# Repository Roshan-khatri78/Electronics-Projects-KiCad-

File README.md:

# ⚡ KiCad Projects Portfolio

A growing collection of electronics projects designed in **KiCad** — schematics, PCB layouts, and Gerber files. Built as part of my hands-on learning journey in electronics engineering and PCB design.

---

## 📖 About

These projects range from beginner circuits to progressively complex PCB designs. Each one reflects real learning — including mistakes, revisions, and improvements over time. I add new projects regularly as I continue to grow.

**Skills practiced:**
- Schematic capture & symbol assignment
- PCB layout & trace routing
- Footprint selection & custom footprint creation
- Copper pours, DRC, and design rules
- Gerber file export for fabrication
- 3D model linking & visualization
- Hierarchical schematics & multi-sheet designs
- Custom symbol and footprint library creation

---

## 🗂️ Projects

### 1. [1-Channel Relay Driver](./1channelrelay/)
A single-channel relay driver PCB using an NPN transistor (MMBT2222A) to switch a Fujitsu FTR-LYCA005x relay from a microcontroller signal. Includes a flyback diode for back-EMF protection and a decoupling capacitor. All SMD components with a GND copper pour.
- **Key components:** MMBT2222A, FTR-LYCA005x relay, 1N4148 flyback diode
- **Concepts:** NPN switching, flyback protection, SMD layout, copper pour

### 2. [3-Phase BLDC Motor Controller](./3-Phase%20BLDC%20(Brushless%20DC)%20Motor%20Controller/)
A hierarchical, multi-sheet PCB design for driving a 3-phase brushless DC motor, using IR2104 half-bridge gate drivers to switch a 3-phase MOSFET bridge.
- **Key components:** IR2104 gate driver ICs, 3-phase MOSFET bridge
- **Concepts:** Hierarchical schematic design, gate driver circuits, 3-phase commutation, ERC debugging across multiple sheets

### 3. [Battery Desulfator Circuit](./Battery%20Desulfator%20circuit/)
An NE555-based pulse generator circuit designed to desulfate lead-acid batteries by sending high-frequency pulses to break down lead sulfate crystals on battery plates. Uses the DISCH pin (pin 7) to drive an IRF244V MOSFET and a flyback inductor (L1).
- **Key components:** NE555 timer IC, IRF244V MOSFET
- **Concepts:** 555 astable mode, pulse generation, MOSFET gate drive, battery maintenance circuits

### 4. [3V to 40V DC Booster](./3v%20to%2040v%20DC%20booster/)
A DC-DC boost converter PCB that steps up voltage from 3V to up to 40V. Designed for applications requiring higher voltages from low-voltage power supplies.
- **Concepts:** Boost converter topology, inductor selection, PCB layout for power electronics

### 5. [60W SMPS](./60w%20smps/)
A 60-watt Switch-Mode Power Supply (SMPS) PCB design. SMPS circuits offer high efficiency compared to linear regulators by using high-frequency switching to regulate output voltage.
- **Concepts:** Switching power supply topology, high-frequency PCB layout, power conversion, isolation

### 6. [Air Quality Sensor Board](./Air%20Quality%20Sensor%20Board/)
A sensor board PCB for monitoring air quality, pairing an air quality sensor with a microcontroller interface and a Tag-Connect SWD programming footprint for debugging.
- **Key components:** Air quality sensor IC, MCU, Tag-Connect SWD header
- **Concepts:** Analog sensor interfacing, board outline (Edge.Cuts) definition, DRC-clean layout, SWD footprint sourcing

### 7. [Arduino Uno R3 Clone](./Arduino%20R3/)
A faithful clone of the classic Arduino Uno R3, built around the ATmega328P microcontroller, replicating the original reference design.
- **Key components:** ATmega328P (DIP-28), 16MHz crystal, USB-to-serial interface
- **Concepts:** Reference design replication, footprint/symbol matching, copper pour strategy, through-hole MCU layout

### 8. [DC-DC Buck Converter (XL4015 CC/CV)](./DC-DC%20Buck%20converter/)
A step-down converter PCB based on the XL4015 IC, providing constant-current/constant-voltage (CC/CV) regulated output for charging and general power applications.
- **Key components:** XL4015 buck converter IC
- **Concepts:** CC/CV regulation, power inductor selection, feedback loop layout, thermal considerations

### 9. [DS3231 RTC Module](./DS3231%20RTC%20Module/)
A real-time clock breakout board built around the DS3231 high-precision RTC IC with battery backup, for timekeeping in embedded systems.
- **Key components:** DS3231 RTC IC, coin cell battery backup
- **Concepts:** RTC interfacing over I2C, battery backup circuit design, breakout board layout

### 10. [HC-06 Bluetooth Module](./HC-06%20BLUETOOTH%C2%AE%20Module/)
A breakout/reference design board for the HC-06 Bluetooth serial module, enabling wireless UART communication for microcontroller projects.
- **Key components:** HC-06 Bluetooth serial module
- **Concepts:** Module-level symbol/footprint sourcing, wireless UART bridging, breakout board design

### 11. [Induction Heater](./inductionheater/)
An induction heater circuit PCB. Uses high-frequency switching to generate an alternating magnetic field in a work coil, inducing eddy currents in conductive materials to produce heat.
- **Concepts:** High-frequency switching, resonant circuits, power PCB layout

### 12. [Mini Inverter](./mini%20inverter/)
A mini inverter circuit using IR2153 gate drive circuitry to convert DC to AC. The IR2153 provides high-side and low-side gate drive signals for a half-bridge MOSFET configuration.
- **Key components:** IR2153 gate driver
- **Concepts:** DC-AC inversion, gate drive circuits, half-bridge topology, IR2153 oscillator

### 13. [L298 Motor Driver](./L298%20motor%20driver/)
A motor driver PCB based on the L298N dual H-bridge IC, capable of driving two DC motors or one stepper motor with direction and speed control. Designed with onboard power regulation and protection diodes.
- **Key components:** L298N dual H-bridge IC
- **Concepts:** H-bridge motor control, dual DC/stepper motor drive, flyback diode protection, PCB layout for moderate current loads

### 14. [LED Flasher](./LED%20flasher/)
A simple astable multivibrator LED flasher circuit. A foundational circuit demonstrating oscillator design and timing with discrete components or a 555 timer.
- **Concepts:** Astable oscillator, RC timing, LED drive, beginner PCB layout

### 15. [SPO2 (Pulse Oximeter)](./SPO2/)
A pulse oximeter circuit PCB for measuring blood oxygen saturation (SpO2) and heart rate. Uses IR and red LEDs with a photodetector to sense light absorption differences in oxygenated vs. deoxygenated blood.
- **Concepts:** Optical sensing, analog signal conditioning, biopotential measurement, photodetector interfacing

### 16. [STM32 DEV Board](./STM32%20DEV%20board/)
A custom development board PCB for the STM32 microcontroller family. Includes necessary support circuitry such as decoupling capacitors, reset circuitry, boot mode selection, and programming headers.
- **Key components:** STM32 microcontroller
- **Concepts:** Microcontroller PCB design, power decoupling, SWD/JTAG programming interface, crystal oscillator layout

### 17. [USB to UART Converter](./USB2UART/)
A USB-to-UART bridge PCB for serial communication between a PC and embedded systems. Used for programming and debugging microcontrollers that lack native USB support.
- **Key components:** USB-UART bridge IC (e.g. CH340/CP2102)
- **Concepts:** USB full-speed interface, UART protocol, level shifting, USB connector footprint, ESD protection

### 18. [ESP32 Demo Project](./esp32%20demo%20project/)
A demonstration PCB built around the ESP32 module, exploring its GPIO, power, and communication capabilities. Serves as a base reference design for ESP32-based projects.
- **Key components:** ESP32 module
- **Concepts:** ESP32 power requirements, decoupling, RF layout considerations, boot mode strapping pins

### 19. [ESP32 Drone (Flight Controller)](./esp32Drone/)
An ESP32-based quadcopter flight controller PCB. Integrates IMU sensing, ESC signal output, power distribution, and communication interfaces in a compact layout suitable for a drone frame.
- **Key components:** ESP32, IMU (e.g. MPU-6050/ICM-42688), USB-C
- **Concepts:** Flight controller architecture, IMU interfacing, PWM/DSHOT ESC output, hierarchical schematics, 4-layer PCB layout, USB-C power delivery

### 20. [Microcontroller-Controlled Digital Radio Receiver](./microcontroller-controlled%20digital%20radio%20receiver/)
A digital radio receiver PCB controlled by a microcontroller, enabling tuning and control of FM/AM radio stations via software. Combines RF front-end with digital control logic.
- **Key components:** Radio receiver IC, microcontroller
- **Concepts:** RF signal reception, I2C/SPI control interface, audio output, antenna design considerations

### 21. [One Digit Up/Down Counter](./one%20digit%20updown%20counter/)
A single-digit up/down counter circuit with a 7-segment display, driven by logic ICs or a microcontroller. Counts up or down based on input signals.
- **Key components:** Up/down counter IC, 7-segment display
- **Concepts:** Digital counting logic, BCD to 7-segment decoding, push-button debouncing, display drive

### 22. [Portable FM Radio Receiver](./portable%20FM%20radio%20receiver/)
A portable FM radio receiver PCB using a dedicated FM receiver IC, designed for battery-powered operation. Includes audio output and tuning interface in a compact layout.
- **Key components:** FM receiver IC (M6955), Arduino Pro Mini
- **Concepts:** FM demodulation, audio amplification, hierarchical schematic design, compact 4-layer PCB layout, custom symbol creation

### 23. [ESP32 Oscilloscope & Function Generator](./ESP32_OSCILLOSCOPE_AND_FN_GENERATOR/) 🎓 *Final Year Project*
An ESP32-based oscilloscope and function generator PCB for the BEICE final year project (FYP). Combines signal acquisition (oscilloscope) and signal synthesis (function generator) in a single instrument platform.
- **Key components:** ESP32, ADC/DAC circuitry, op-amps
- **Concepts:** High-speed signal sampling, DAC waveform generation, analog front-end design, instrument PCB layout, hierarchical schematics

### 24. [Analog Soldering Station Kit](./analog%20soldering%20station%20kit/)
An analog temperature-controlled soldering station PCB. Uses feedback from the soldering iron's thermocouple or temperature sensor to regulate tip temperature via PWM power control.
- **Key components:** TL494 PWM controller, LM358 op-amp
- **Concepts:** Closed-loop temperature control, PWM power regulation, thermocouple signal conditioning, analog feedback design

---

## 📁 Repository Structure

```
Electronics-Projects-KiCad-/
├── 1channelrelay/
├── 3-Phase BLDC (Brushless DC) Motor Controller/
├── 3v to 40v DC booster/
├── 60w smps/
├── Air Quality Sensor Board/
├── analog soldering station kit/
├── Arduino R3/
├── Battery Desulfator circuit/
├── DC-DC Buck converter/
├── DS3231 RTC Module/
├── esp32 demo project/
├── esp32Drone/
├── ESP32_OSCILLOSCOPE_AND_FN_GENERATOR/
├── HC-06 BLUETOOTH® Module/
├── inductionheater/
├── L298 motor driver/
├── LED flasher/
├── microcontroller-controlled digital radio receiver/
├── mini inverter/
├── one digit updown counter/
├── portable FM radio receiver/
├── SPO2/
├── STM32 DEV board/
├── USB2UART/
├── .gitignore
└── README.md
```

Each project folder contains:
```
<project-name>/
├── *.kicad_sch      # Schematic files
├── *.kicad_pcb      # PCB layout files
└── Gerber/          # Fabrication-ready Gerber exports
```

---

## 🛠️ Tools Used

- **KiCad EDA** (v10.0)
- Manufacturer datasheets for component selection
- KiCad 3D viewer for visual inspection
- Custom symbol & footprint libraries

---

## 📝 Note on Quality

These projects document my learning process openly. Some designs may have imperfections or areas for improvement — that's intentional. I revisit and improve designs as my knowledge grows rather than hiding earlier work.

---

## 📄 License

Unless otherwise stated, all projects in this repository are shared for educational and portfolio purposes.

Feel free to open an issue or start a discussion if you have suggestions or feedback.

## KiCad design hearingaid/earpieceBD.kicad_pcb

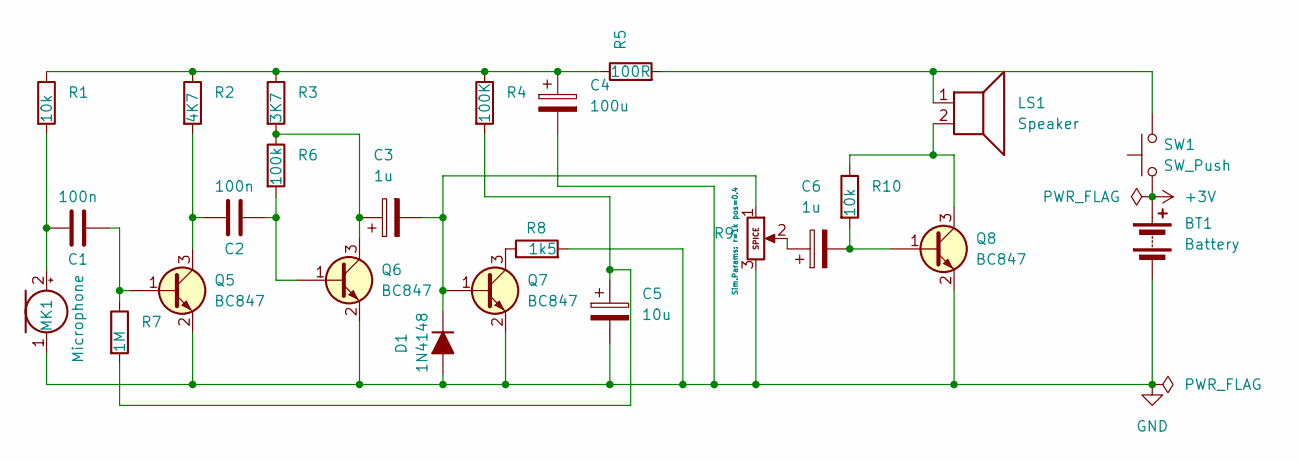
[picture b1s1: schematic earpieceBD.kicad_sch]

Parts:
BT1: Battery; BatteryHolder_Renata_SMTU2032-LF_1x2032
C1, C2: 100n; C_0805_2012Metric_Pad1.18x1.45mm_HandSolder
C3, C6: 1u; CP_EIA-3216-18_Kemet-A
C4: 100u; CP_Elec_5x5.4
C5: 10u; CP_EIA-3216-18_Kemet-A
D1: 1N4148; D_SOD-123
LS1: Speaker; SPKR_CVS-1708
MK1: Microphone; MIC_CMEJ-0415-42-P
Q5, Q6, Q7, Q8: BC847; SOT-23
R1, R10: 10k; R_0805_2012Metric_Pad1.20x1.40mm_HandSolder
R2: 4K7; R_0805_2012Metric_Pad1.20x1.40mm_HandSolder
R3: 3K7; R_0805_2012Metric_Pad1.20x1.40mm_HandSolder
R4: 100K; R_0805_2012Metric_Pad1.20x1.40mm_HandSolder
R5: 100R; R_0805_2012Metric_Pad1.20x1.40mm_HandSolder
R6: 100k; R_0805_2012Metric_Pad1.20x1.40mm_HandSolder
R7: 1M; R_0805_2012Metric_Pad1.20x1.40mm_HandSolder
R8: 1k5; R_0805_2012Metric_Pad1.20x1.40mm_HandSolder
R9: 22k; Potentiometer_Bourns_3314G_Vertical
SW1: SW_Push; SW_SPST_EVQP2_MiddlePushTravel_H2.5mm

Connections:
+3V: BT1.1 (+), SW1.1
GND: BT1.2 (-), C4.2, C5.2, D1.2 (A), MK1.1 (-), Q5.2 (E), Q6.2 (E), Q7.2 (E), Q8.2 (E), R8.2, R9.3
unnamed: C4.1, R1.1, R2.1, R3.1, R4.1, R5.1
unnamed: C5.1, R4.2, R7.2
unnamed: C6.1, R9.2
unnamed: C3.2, D1.1 (K), Q7.1 (B), R9.1
unnamed: LS1.1, R5.2, SW1.2
unnamed: C1.1, MK1.2 (+), R1.2
unnamed: C1.2, Q5.1 (B), R7.1
unnamed: C2.1, Q5.3 (C), R2.2
unnamed: C2.2, Q6.1 (B), R6.2
unnamed: C3.1, Q6.3 (C), R3.2, R6.1
unnamed: Q7.3 (C), R8.1
unnamed: C6.2, Q8.1 (B), R10.2
unnamed: LS1.2, Q8.3 (C), R10.1

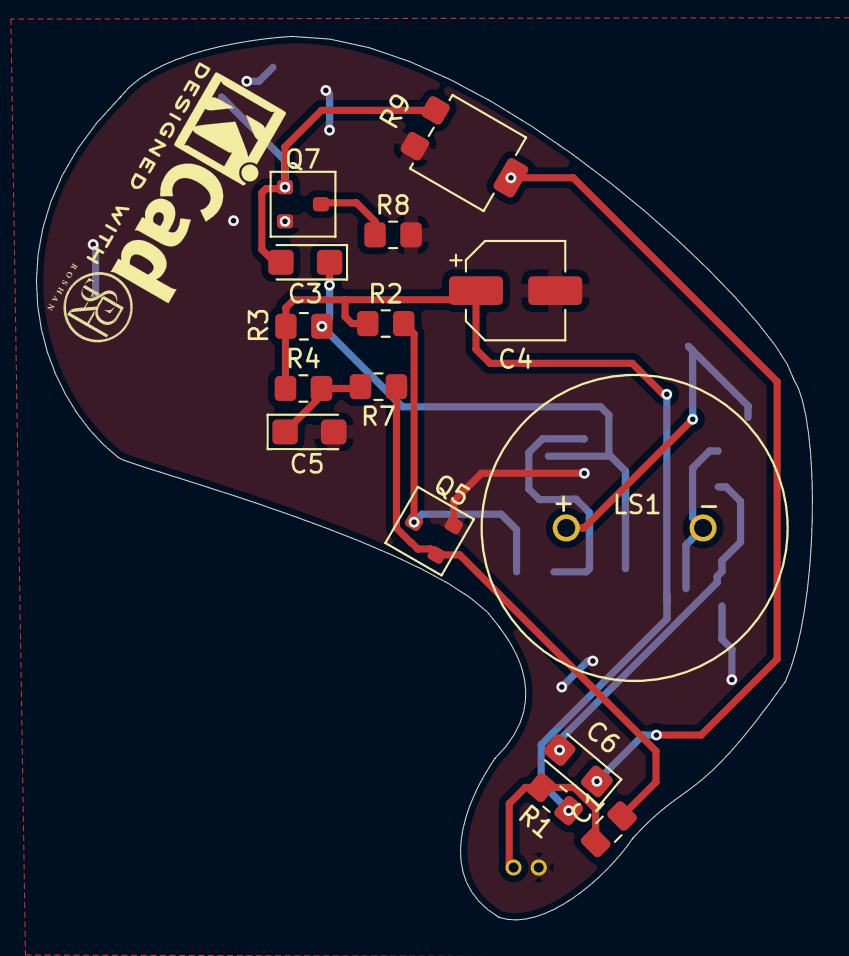
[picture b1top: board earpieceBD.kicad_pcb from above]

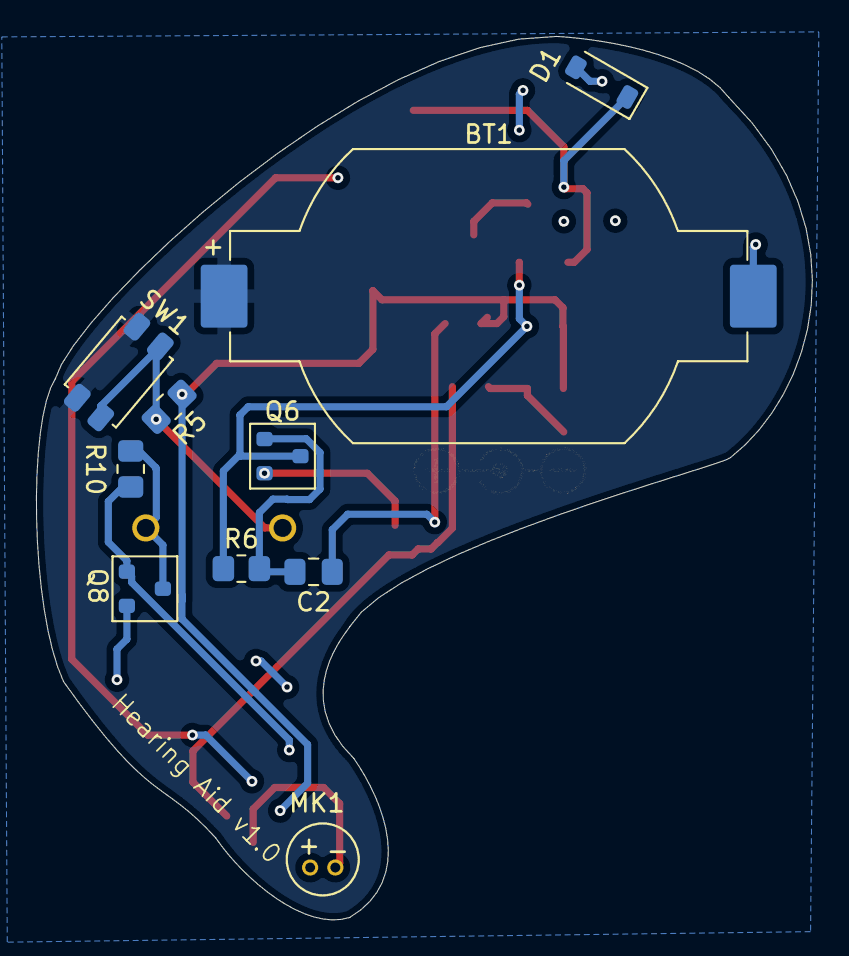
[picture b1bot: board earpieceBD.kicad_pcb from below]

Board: 4 copper layers, 43.1 x 49.1 mm, 25 parts (10 on the bottom side), 15 nets.

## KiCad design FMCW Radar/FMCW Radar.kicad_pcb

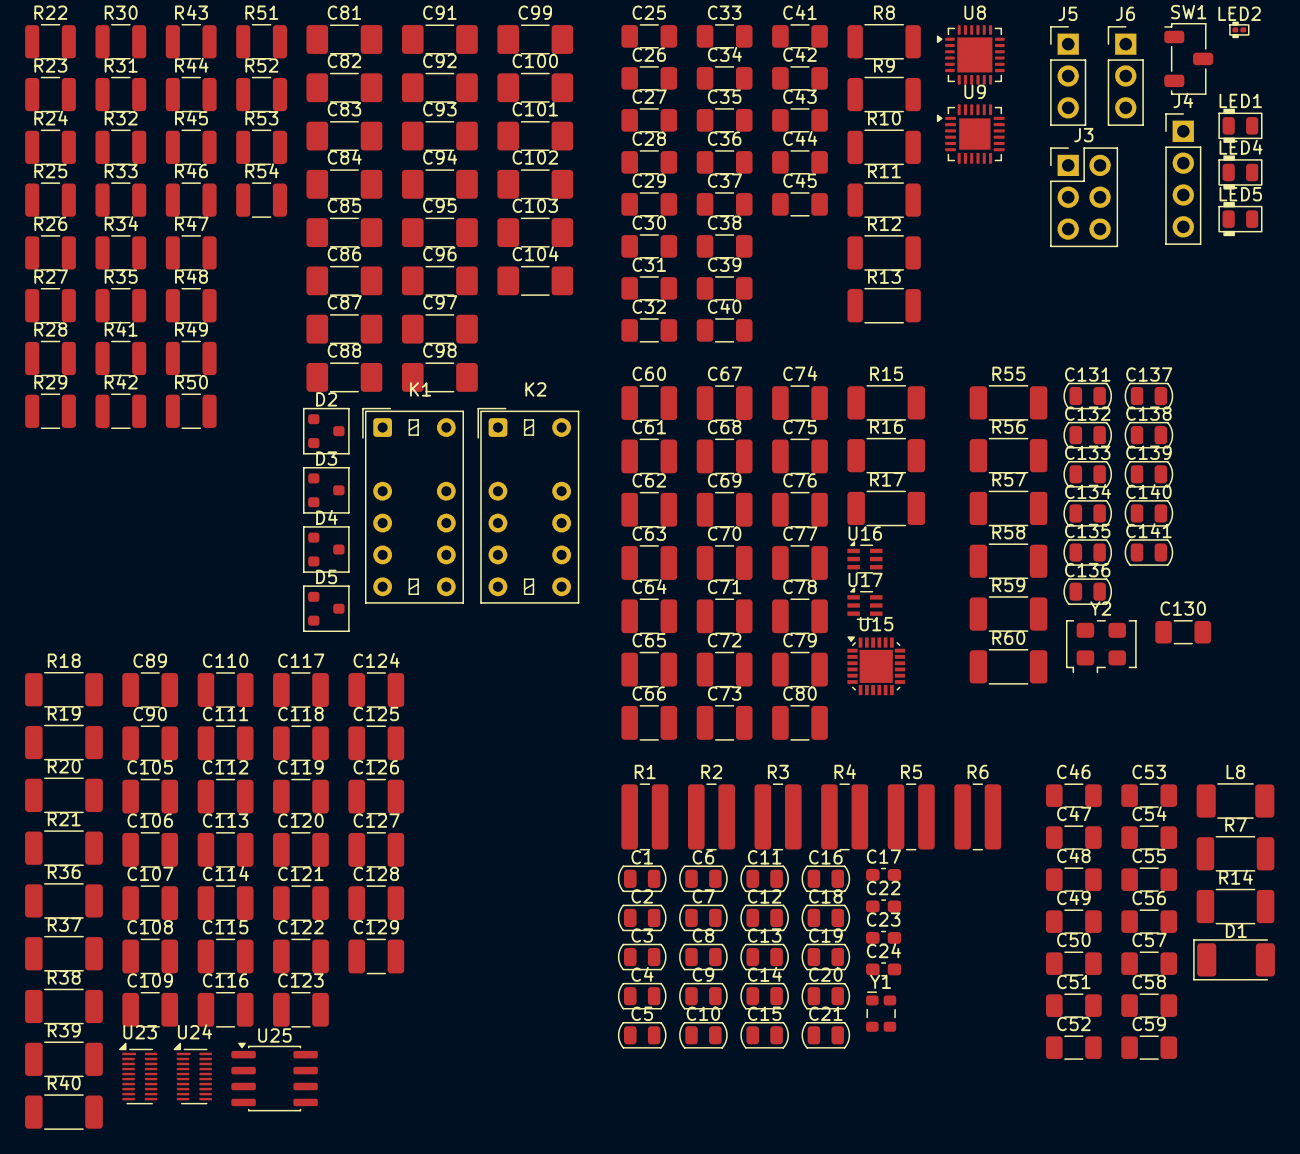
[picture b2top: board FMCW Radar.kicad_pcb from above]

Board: 2 copper layers, 228 parts (0 on the bottom side), 101 nets, no tracks yet.

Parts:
C1, C2, C7, C10, C140: 1u; C_0805_2012Metric
C3, C4, C5, C6, C9, C11, C16, C131, C133, C134, C136, C138, C139: 100n; C_0805_2012Metric
C8: 10on; C_0805_2012Metric
C12, C13, C14, C15, C18, C19, C20, C21: 4u7; C_0805_2012Metric
C17: C_0805; C_0603_1608Metric_Pad1.08x0.95mm_HandSolder
C22, C24: 10n; C_0603_1608Metric_Pad1.08x0.95mm_HandSolder
C23: 22n; C_0603_1608Metric_Pad1.08x0.95mm_HandSolder
C25, C26, C27, C28: 4U7; C_1206_3216Metric_Pad1.33x1.80mm_HandSolder
C29, C30, C31, C59: 10p; C_1206_3216Metric_Pad1.33x1.80mm_HandSolder
C32: 10n; C_1206_3216Metric_Pad1.33x1.80mm_HandSolder
C33: 4u7; C_1206_3216Metric_Pad1.33x1.80mm_HandSolder
C34: 180n; C_1206_3216Metric_Pad1.33x1.80mm_HandSolder
C35, C37, C38, C39, C40, C41, C42, C43, C44, C45: 15N; C_1206_3216Metric_Pad1.33x1.80mm_HandSolder
C36: 5n6; C_1206_3216Metric_Pad1.33x1.80mm_HandSolder
C46, C56: 100P; C_1206_3216Metric_Pad1.33x1.80mm_HandSolder
C47, C48, C53, C54, C130: 2u2; C_1206_3216Metric_Pad1.33x1.80mm_HandSolder
C49, C50, C51, C52, C55: 100n; C_1206_3216Metric_Pad1.33x1.80mm_HandSolder
C57: 200f; C_1206_3216Metric_Pad1.33x1.80mm_HandSolder
C58: 5p6; C_1206_3216Metric_Pad1.33x1.80mm_HandSolder
C60, C61, C62, C63: 3p; C_1210_3225Metric_Pad1.33x2.70mm_HandSolder
C64: 10P; C_1210_3225Metric_Pad1.33x2.70mm_HandSolder
C65: 10p; C_1210_3225Metric_Pad1.33x2.70mm_HandSolder
C66, C67, C70, C71, C75, C76, C80, C89, C107, C110, C112, C114, C115, C119, C120, C123, C124: 100n; C_1210_3225Metric_Pad1.33x2.70mm_HandSolder
C68, C69, C79: 100p; C_1210_3225Metric_Pad1.33x2.70mm_HandSolder
C72, C117, C121, C126, C128: 4u7; C_1210_3225Metric_Pad1.33x2.70mm_HandSolder
C73, C74, C118, C122, C127, C129: 2u2; C_1210_3225Metric_Pad1.33x2.70mm_HandSolder
C77, C78: 82n; C_1210_3225Metric_Pad1.33x2.70mm_HandSolder
C81, C82, C92, C96: 1u; C_1808_4520Metric_Pad1.72x2.30mm_HandSolder
C83, C84, C86, C88, C91, C94, C95, C100: 33n; C_1808_4520Metric_Pad1.72x2.30mm_HandSolder
C85, C87, C93, C99, C103, C104: 1n1; C_1808_4520Metric_Pad1.72x2.30mm_HandSolder
C90: 10N; C_1210_3225Metric_Pad1.33x2.70mm_HandSolder
C97, C98, C101, C102: 100n; C_1808_4520Metric_Pad1.72x2.30mm_HandSolder
C105: 1U; C_1210_3225Metric_Pad1.33x2.70mm_HandSolder
C106, C116, C125: 1u; C_1210_3225Metric_Pad1.33x2.70mm_HandSolder
C108, C109, C111, C113: 1n; C_1210_3225Metric_Pad1.33x2.70mm_HandSolder
C132, C135, C137, C141: 2u2; C_0805_2012Metric
D1: LED; LED_2010_5025Metric_Pad1.52x2.65mm_HandSolder
D2, D3, D4, D5: BAR46; SOT-23
J3: Conn_02x03_Odd_Even; PinHeader_2x03_P2.54mm_Vertical
J4: Conn_01x04; PinHeader_1x04_P2.54mm_Vertical
J5, J6: Conn_01x03; PinHeader_1x03_P2.54mm_Vertical
K1, K2: EC2-4.5TNU; Relay_DPDT_Kemet_EC2_NU_DoubleCoil
L8: 18n; L_2010_5025Metric_Pad1.52x2.65mm_HandSolder
LED1: LED_0805_Amber; LED_0805_2012Metric
LED2: LED_0201_Red; LED_0201_0603Metric
LED4, LED5: LED_0805_Green; LED_0805_2012Metric
R1, R2, R3, R4: 40K; R_1020_2550Metric_Pad1.33x5.20mm_HandSolder
R5, R6: 470k; R_1020_2550Metric_Pad1.33x5.20mm_HandSolder
R7: 3K9; R_2010_5025Metric_Pad1.40x2.65mm_HandSolder
R8: 49r9; R_2010_5025Metric
R9, R10: 180R; R_2010_5025Metric
R11: 45R3; R_2010_5025Metric
R12: 27r; R_2010_5025Metric
R13: 5K1; R_2010_5025Metric
R14: 680R; R_2010_5025Metric_Pad1.40x2.65mm_HandSolder
R15, R16: 49R9; R_2010_5025Metric_Pad1.40x2.65mm_HandSolder
R17: 665R; R_2010_5025Metric_Pad1.40x2.65mm_HandSolder
R18, R38: 40K; R_2010_5025Metric_Pad1.40x2.65mm_HandSolder
R19: 27r; R_2010_5025Metric_Pad1.40x2.65mm_HandSolder
R20: 1k5; R_2010_5025Metric_Pad1.40x2.65mm_HandSolder
R21: 19r9; R_2010_5025Metric_Pad1.40x2.65mm_HandSolder
R22, R23, R32, R33, R43, R44, R49, R50: 160R; R_1210_3225Metric
R24, R25, R30, R31, R41, R42, R47, R48: 240R; R_1210_3225Metric
R26, R29: 360R; R_1210_3225Metric
R27, R28, R34, R35, R45, R46, R51, R52: 481R; R_1210_3225Metric
R36, R37: 49r9; R_2010_5025Metric_Pad1.40x2.65mm_HandSolder
R39: 8K2; R_2010_5025Metric_Pad1.40x2.65mm_HandSolder
R40: 4K22; R_2010_5025Metric_Pad1.40x2.65mm_HandSolder
R53, R54: 4K22; R_1210_3225Metric
R55, R59: 10k; R_2010_5025Metric_Pad1.40x2.65mm_HandSolder
R56: 5k1; R_2010_5025Metric_Pad1.40x2.65mm_HandSolder
R57: 100k; R_2010_5025Metric_Pad1.40x2.65mm_HandSolder
R58: 0R; R_2010_5025Metric_Pad1.40x2.65mm_HandSolder
R60: 39R; R_2010_5025Metric_Pad1.40x2.65mm_HandSolder
SW1: SW_SPDT; Nidec_Copal_CAS-120A
U8: HMC431; QFN-24-1EP_4x4mm_P0.5mm_EP2.8x2.8mm
U9: ADF4158; LFCSP-24-1EP_4x4mm_P0.5mm_EP2.5x2.5mm
U15: ADL5801; LFCSP-VQ-24-1EP_4x4mm_P0.5mm_EP2.642x2.642mm
U16, U17: 5400BL15B050; Balun_Johanson_5400BL15B050E
U23, U24: TXB0108DQSR; USON-20_2x4mm_P0.4mm
U25: INA849D; SOIC-8_3.9x4.9mm_P1.27mm
Y1: TG2520SMN-xx.xxxxxxMhz-xxxxNM; Oscillator_SMD_SeikoEpson_TG2520SMN-xxx-xxxxxx-4Pin_2.5x2.0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
Y2: TXC-7C; Oscillator_SMD_TXC_7C-4Pin_5.0x3.2mm

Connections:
+3V3A: C38.2, C39.2, C40.2, C47.1, C50.1, U9.6 (AVDD), U9.7 (AVDD), U9.8 (AVDD)
+3V3D: C5.1, C6.1, C7.1, C8.1, C9.1, C10.1, C11.1, C12.1, C13.1, C17.1, C41.1, C42.1, C43.1, C121.1, C138.2, C139.2, C140.2, C141.2, J3.4, J5.1, J6.1, LED1.2 (A), LED2.2 (A), LED4.2 (A), LED5.2 (A), SW1.1 (A)
+3VA: C32.2, C33.2, U8.20 (VCC)
+5V-ADC: C107.1, C108.1, C109.1, C110.1, C111.1, C112.1, C127.1, U25.8 (Vs+)
+5VA: C25.1, C26.1, C53.1, C126.1, R17.2
+5VD: C113.1, C114.1, C117.1, C136.2, C137.2, D2.3 (K), D3.3 (K), D4.3 (K), D5.3 (K), K1.7, K1.12, K2.7, K2.12
-5V-ADC: C89.1, C115.1, C116.1, C125.1, C129.1, U25.5 (Vs-)
/U_MCU/CLK-VDD: C18.1, C19.1, C20.1, C21.1
/U_MCU/MCU-VDDA: C1.1, C2.1, C3.1, C4.1
/U_RxADC/ADC-CLK: U23.3 (A3), U23.11 (B8)
/U_RxADC/ADC-GAIN: U23.2 (A2), U23.12 (B7)
/U_RxADC/ADC-IF N: K2.4, R36.1, U25.4 (+)
/U_RxADC/ADC-IF P: K2.9, R21.2, U25.1 (-)
/U_RxADC/ADC-OF: R39.1, R40.1, R40.2
/U_RxADC/LVL1-OE: R38.1, U24.6 (OE)
/U_RxADC/LVL2-OE: R18.1, U23.6 (OE)
/U_RxADC/LVL-VCCA: C122.1, C123.1, C124.1, U23.5 (VCCA), U24.5 (VCCA)
/U_RxADC/LVL-VCCB: C118.1, C119.1, C120.1, U23.16 (VCCB), U24.16 (VCCB)
/U_RxFrontEnd/LNA2-EN: C59.2, R14.2
/U_RxIFStage/FILT-LR-OUT N: C101.2, K2.10
/U_RxIFStage/FILT-LR-OUT P: C102.2, K2.3
/U_RxIFStage/FILT-RST: D2.1 (A), D3.1 (A), K1.6, K2.6
/U_RxIFStage/FILT-SET: D4.1 (A), D5.1 (A), K1.1, K2.1
/U_RxIFStage/FILT-SR-IN N: K1.8, K1.10, R24.1, R26.2, R29.1, R31.1
/U_RxIFStage/FILT-SR-IN P: K1.3, K1.5, R25.1, R26.1, R29.2, R30.1
/U_RxIFStage/FILT-SR-OUT N: C97.2, K2.8
/U_RxIFStage/FILT-SR-OUT P: C98.2, K2.5
/U_RxMixer/BALLUN-LO N: C61.1, U17.3
/U_RxMixer/BALLUN-LO P: C60.1, U17.4
/U_RxMixer/BALLUN-RF N: C62.1, U16.4
/U_RxMixer/BALLUN-RF P: C63.1, U16.3
/U_RxMixer/MIX-LO N: C61.2, U15.3 (LOIP)
/U_RxMixer/MIX-LO P: C60.2, U15.4 (LOIN)
/U_RxMixer/MIX-RF N: C62.2, U15.15 (RFIN)
/U_RxMixer/MIX-RF P: C63.2, U15.16 (RFIP)
/U_StatusAndInputOutput/BOOT0: J5.2, R2.1
/U_StatusAndInputOutput/BOOT1: J6.2, R4.2
/U_StatusAndInputOutput/MISC1: J4.2, J4.4
/U_StatusAndInputOutput/SWD-NRST: C16.1, J3.2
/U_StatusAndInputOutput/TX/STDBY: R1.2, SW1.2 (B)
GND: C1.2, C2.2, C3.2, C4.2, C5.2, C6.2, C7.2, C8.2, C9.2, C10.2, C11.2, C12.2, C13.2, C14.2, C15.2, C16.2, C17.2, C18.2, C19.2, C20.2, C21.2, C22.2, C24.1, C25.2, C26.2, C27.2, C28.2, C30.2, C31.1, C32.1, C33.1, C35.1, C36.1, C37.1, C38.1, C39.1, C40.1, C41.2, C42.2, C43.2, C44.2, C45.2, C46.2, C47.2, C48.2, C49.2, C50.2, C52.1, C53.2, C54.2, C55.2, C56.2, C57.2, C59.1, C66.2, C67.2, C68.2, C69.2, C70.2, C71.2, C72.2, C73.2, C74.2, C75.2, C76.2, C79.1, C80.1, C81.2, C82.2, C89.2, C90.2, C92.2, C96.2, C103.1, C104.1, C105.2, C106.2, C107.2, C108.2, C109.2, C110.2, C111.2, C112.2, C113.2, C114.2, C115.2, C116.2, C117.2, C118.2, C119.2, C120.2, C121.2, C122.2, C123.2, C124.2, C125.2, C126.2, C127.2, C128.2, C129.2, C130.2, C131.1, C132.1, C133.1, C134.1, C135.1, C136.1, C137.1, C138.1, C139.1, C140.1, C141.1, D1.1 (K), J3.3, J4.1, J4.3, J5.3, J6.3, R3.2, R8.2, R10.1, R13.1, R18.2, R37.1, R38.2, R56.1, R58.1, R59.2, SW1.3 (C), U8.15 (GND), U8.25 (GND), U9.1 (CPGND), U9.2 (AGND), U9.3 (AGND), U9.10 (DGND), U9.11 (SDGND), U9.18 (SDVDD), U9.19 (DVDD), U9.25 (AGND), U15.1 (GND), U15.2 (GND), U15.5 (GND), U15.6 (GND), U15.8 (GND), U15.12 (GND), U15.14 (GND), U15.17 (GND), U15.19 (GND), U15.23 (GND), U15.25 (GND), U16.2 (GND), U16.5 (GND), U17.2 (GND), U17.5 (GND), U23.15 (GND), U24.15 (GND), U25.6 (Ref), Y1.2 (GND), Y2.2 (GND)
unnamed: C22.1, R5.1, R6.2
unnamed: C34.1, R10.2, R12.1
unnamed: C34.2, C35.2, R9.1
unnamed: C44.1, C45.1
unnamed: C46.1, C48.1, C49.1
unnamed: C54.1, C55.1, C56.1, L8.1, R7.2
unnamed: C64.2, U17.1
unnamed: C65.2, U16.1
unnamed: C72.1, C73.1, C74.1, C75.1, C76.1, R15.1, R16.1
unnamed: C83.1, R23.1, R24.2, R28.1
unnamed: C83.2, R22.1, R25.2, R27.1
unnamed: C86.1, R30.2, R32.1, R34.1
unnamed: C86.2, R31.2, R33.1, R35.1
unnamed: C91.1, R41.2, R43.1, R45.1
unnamed: C91.2, R42.2, R44.1, R46.1
unnamed: C95.1, R47.2, R49.1, R51.1
unnamed: C95.2, R48.2, R50.1, R52.1
unnamed: C130.1, R55.2, R57.2
unnamed: D1.2 (A), R14.1
unnamed: C103.2, R53.2
unnamed: C104.2, R54.2
unnamed: R19.1, U25.7
unnamed: R20.1, U25.3 (Rg)
unnamed: R20.2, U25.2 (Rg)
unnamed: R21.1, R36.2, R37.2
unnamed: C23.2, R5.2
unnamed: C27.1, C28.1
unnamed: C36.2, R9.2, R11.2, U8.22 (VTUNE)
unnamed: C37.2, U9.4 (RFINB)
unnamed: R13.2, U9.23 (RSET)
unnamed: R12.2, U9.20 (SW1)
unnamed: R11.1, U9.21 (SW2)
unnamed: C57.1, C58.2
unnamed: C51.1, C52.2, L8.2
unnamed: C78.1, R15.2, U15.21 (IFON)
unnamed: C77.1, R16.2, U15.20 (IFOP)
unnamed: C66.1, C67.1, C68.1, C69.1, C70.1, C71.1, U15.7 (VPLO), U15.13 (VPDT), U15.18 (VPRF), U15.24 (VPLO)
unnamed: C79.2, C80.2, R17.1, U15.10 (VSET)
unnamed: C85.1, R23.2
unnamed: C84.1, R22.2
unnamed: C84.2, R28.2, R41.1
unnamed: C85.2, R27.2, R42.1
unnamed: C87.1, R32.2
unnamed: C88.1, R33.2
unnamed: C88.2, R34.2, R47.1
unnamed: C87.2, R35.2, R48.1
unnamed: C93.1, R43.2
unnamed: C94.1, R44.2
unnamed: C94.2, C97.1, R45.2
unnamed: C93.2, C98.1, R46.2
unnamed: C99.1, R49.2
unnamed: C100.1, R50.2
unnamed: C100.2, C102.1, R51.2
unnamed: C99.2, C101.1, R52.2
unnamed: C90.1, R19.2
unnamed: C132.2, C133.2
unnamed: C134.2, C135.2
unnamed: C23.1, Y1.3 (OUT)
unnamed: C24.2, Y1.4 (Vcc)
unnamed: C131.2, Y2.4 (Vdd)

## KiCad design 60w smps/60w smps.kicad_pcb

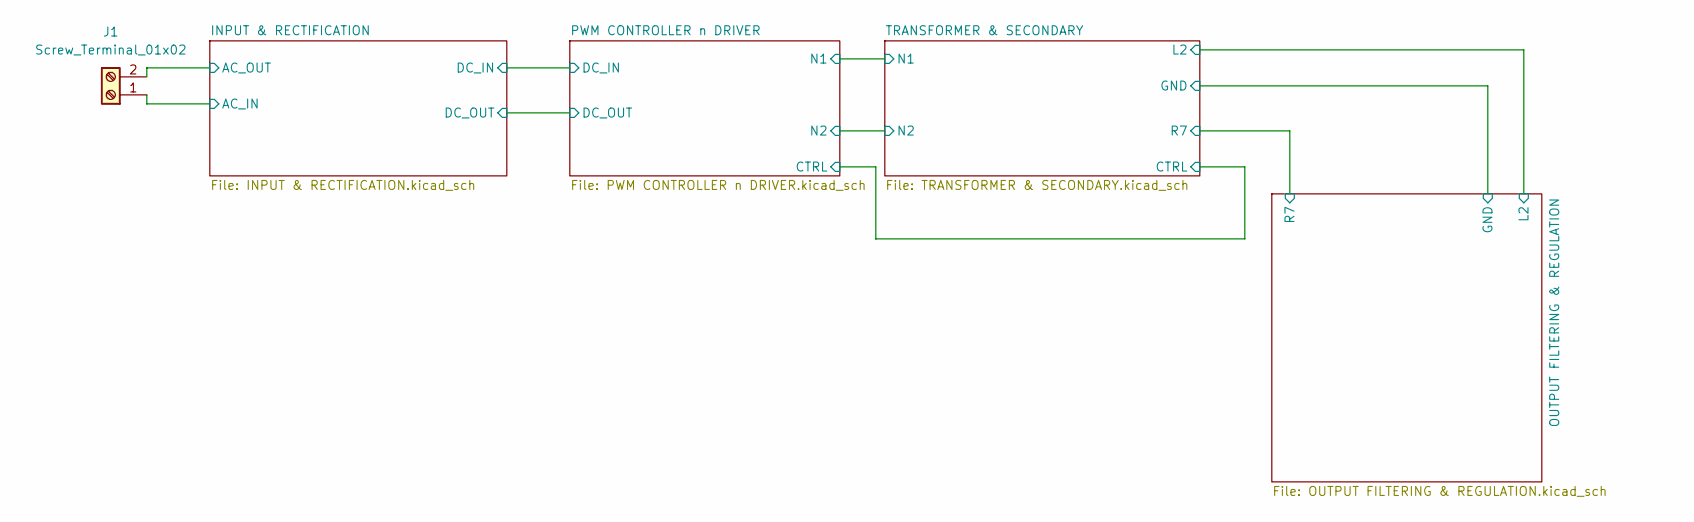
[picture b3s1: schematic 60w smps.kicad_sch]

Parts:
J1: Screw_Terminal_01x02; TerminalBlock_MaiXu_MX126-5.0-02P_1x02_P5.00mm

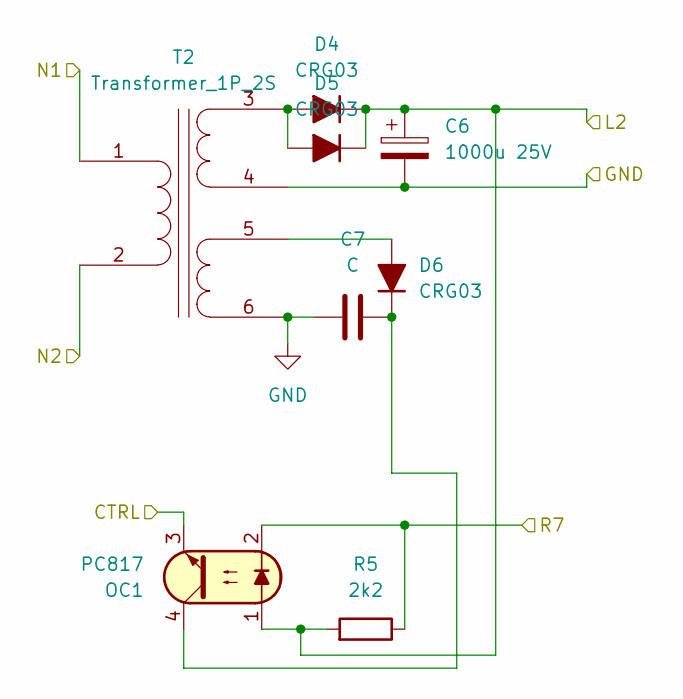
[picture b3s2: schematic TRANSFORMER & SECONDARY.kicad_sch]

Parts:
C6: 1000u 25V; CP_Elec_8x10
C7: C; C_0805_2012Metric_Pad1.18x1.45mm_HandSolder
D4, D5, D6: CRG03; D_SOD-123F
OC1: PC817; DIP-4_W7.62mm_LongPads
R5: 2k2; R_0805_2012Metric_Pad1.20x1.40mm_HandSolder
T2: Transformer_1P_2S; WE-IBTI_EP7_L9.78W9.5H10.54

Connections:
/INPUT & RECTIFICATION/DC_IN: T2.1 (AA); also elsewhere on the board
/OUTPUT FILTERING & REGULATION/L2: C6.1, D4.1 (K), D5.1 (K), OC1.1, R5.1; also elsewhere on the board
/OUTPUT FILTERING & REGULATION/R7: OC1.2, R5.2; also elsewhere on the board
/PWM CONTROLLER n DRIVER/CTRL: OC1.3; also elsewhere on the board
/PWM CONTROLLER n DRIVER/N2: T2.2 (AB); also elsewhere on the board
GND: C6.2, C7.1, T2.4 (SB), T2.6 (SD); also elsewhere on the board
unnamed: D4.2 (A), D5.2 (A), T2.3 (SA)
unnamed: D6.2 (A), T2.5 (SC)
unnamed: C7.2, D6.1 (K), OC1.4

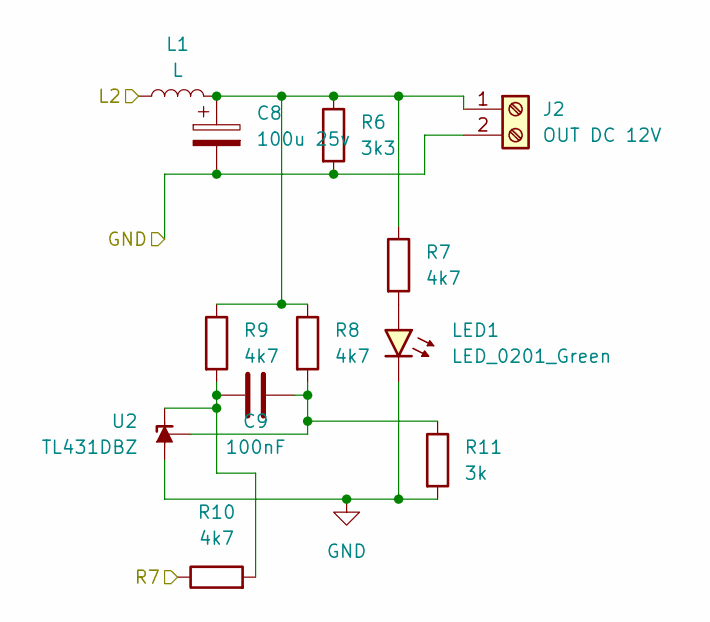
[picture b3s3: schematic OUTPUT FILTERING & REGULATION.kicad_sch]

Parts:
C8: 100u 25v; CP_Radial_D16.0mm_P7.50mm
C9: 100nF; C_1808_4520Metric_Pad1.72x2.30mm_HandSolder
J2: OUT DC 12V; TerminalBlock_MaiXu_MX126-5.0-02P_1x02_P5.00mm
L1: L; L_1008_2520Metric_Pad1.43x2.20mm_HandSolder
LED1: LED_0201_Green; LED_0201_0603Metric
R6: 3k3; R_0603_1608Metric_Pad0.98x0.95mm_HandSolder
R7, R8, R9, R10: 4k7; R_0603_1608Metric_Pad0.98x0.95mm_HandSolder
R11: 3k; R_0603_1608Metric_Pad0.98x0.95mm_HandSolder
U2: TL431DBZ; SOT-23

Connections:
/OUTPUT FILTERING & REGULATION/L2: L1.1; also elsewhere on the board
/OUTPUT FILTERING & REGULATION/R7: R10.1; also elsewhere on the board
GND: C8.2, J2.2, LED1.1 (K), R6.2, R11.2, U2.3 (A); also elsewhere on the board
unnamed 17: C8.1, J2.1, L1.2, R6.1, R7.1, R8.1, R9.1; also elsewhere on the board
unnamed: LED1.2 (A), R7.2
unnamed: C9.1, R9.2, R10.2, U2.1 (K)
unnamed: C9.2, R8.2, R11.1, U2.2 (REF)

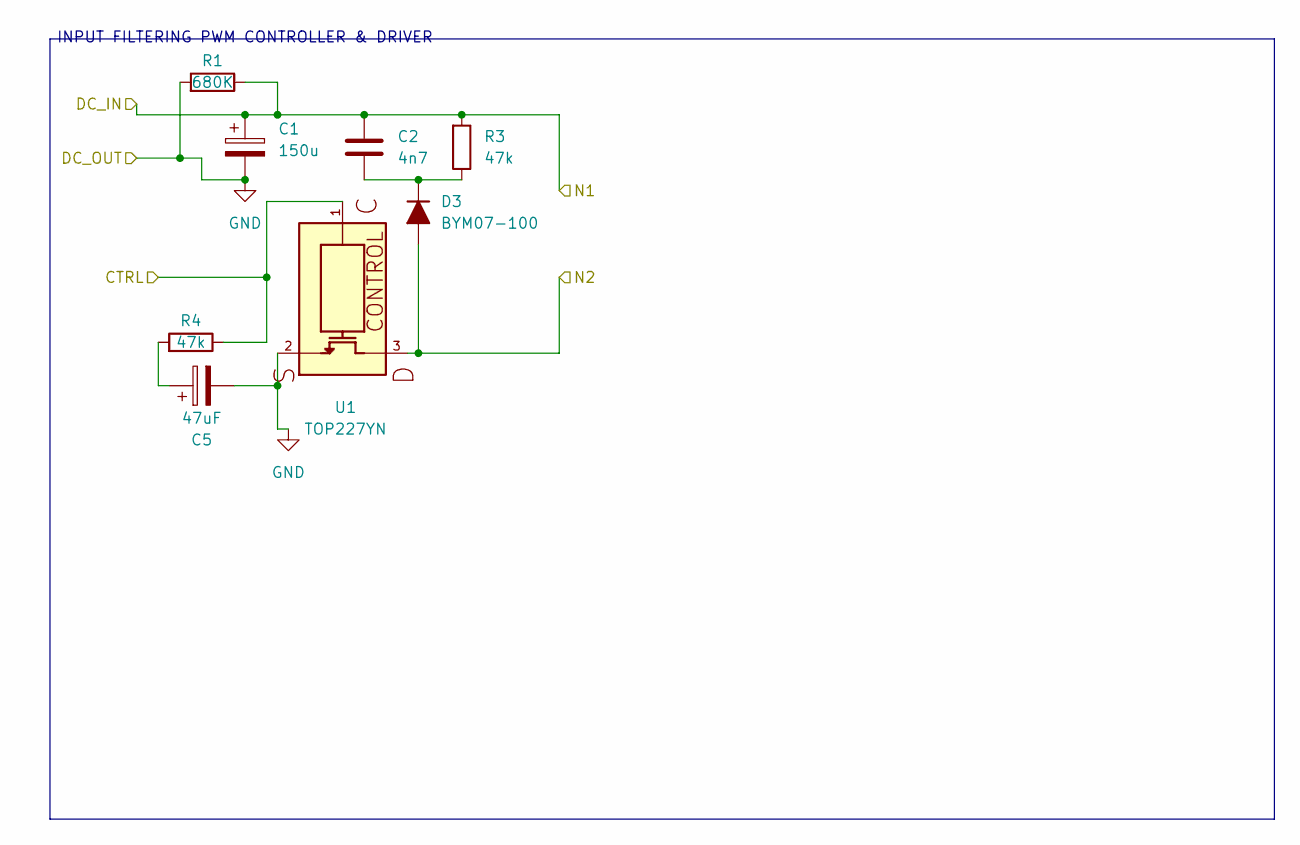
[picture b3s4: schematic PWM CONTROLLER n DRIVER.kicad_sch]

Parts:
C1: 150u; CP_Radial_D10.0mm_P3.50mm
C2: 4n7; C_Axial_L12.0mm_D10.5mm_P15.00mm_Horizontal
C5: 47uF; CP_Radial_D10.0mm_P3.50mm
D3: BYM07-100; D_MiniMELF
R1: 680K; R_0805_2012Metric_Pad1.20x1.40mm_HandSolder
R3, R4: 47k; R_Axial_DIN0414_L11.9mm_D4.5mm_P15.24mm_Horizontal
U1: TOP227YN; TO254P1035X444X2115-3N; PARTREV G

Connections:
/INPUT & RECTIFICATION/DC_IN: C1.1, C2.1, R1.2, R3.1; also elsewhere on the board
/PWM CONTROLLER n DRIVER/CTRL: R4.2, U1.1; also elsewhere on the board
/PWM CONTROLLER n DRIVER/N2: D3.2 (A), U1.3; also elsewhere on the board
GND: C1.2, C5.2, R1.1, U1.2; also elsewhere on the board
unnamed: C5.1, R4.1
unnamed: C2.2, D3.1 (K), R3.2

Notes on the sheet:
INPUT FILTERING PWM CONTROLLER & DRIVER

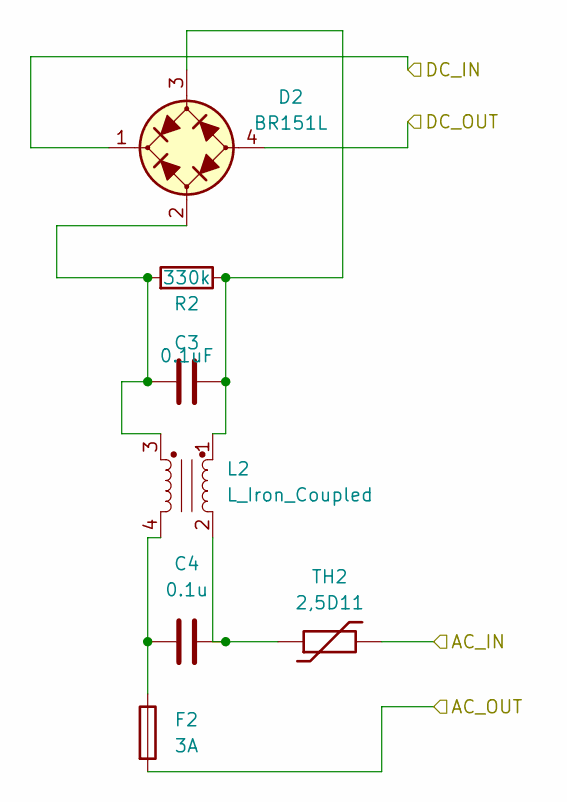
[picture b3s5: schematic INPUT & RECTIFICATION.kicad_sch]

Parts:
C3: 0.1uF; C_2220_5750Metric
C4: 0.1u; C_Axial_L12.0mm_D6.5mm_P20.00mm_Horizontal
D2: BR151L; Diode_Bridge_28.6x28.6x7.3mm_P5.08mm_Vertical
F2: 3A; Fuse_2010_5025Metric_Pad1.52x2.65mm_HandSolder
L2: L_Iron_Coupled; WE-MCRI_1040
R2: 330k; R_0805_2012Metric_Pad1.20x1.40mm_HandSolder
TH2: 2,5D11; R_0815_2038Metric_Pad1.53x4.00mm_HandSolder

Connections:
/INPUT & RECTIFICATION/AC_IN: TH2.2; also elsewhere on the board
/INPUT & RECTIFICATION/AC_OUT: F2.2; also elsewhere on the board
/INPUT & RECTIFICATION/DC_IN: D2.1 (+); also elsewhere on the board
GND: D2.4 (-); also elsewhere on the board
unnamed: C4.1, F2.1, L2.4
unnamed: C4.2, L2.2, TH2.1
unnamed: C3.1, D2.2 (1), L2.3, R2.1
unnamed: C3.2, D2.3 (2), L2.1, R2.2

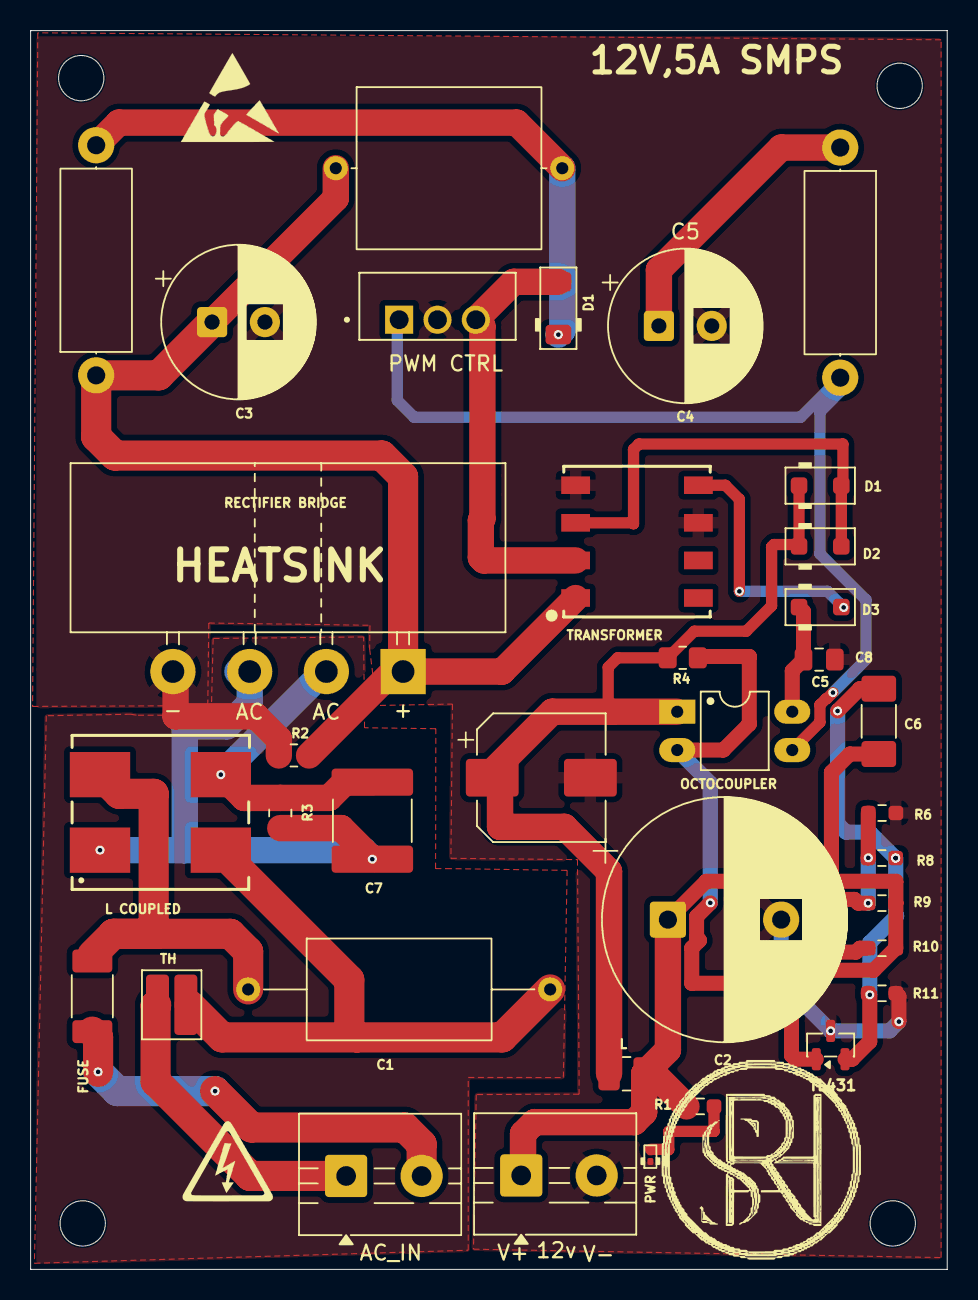
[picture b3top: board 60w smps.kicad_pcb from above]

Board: 2 copper layers, 60.7 x 82.0 mm, 37 parts (0 on the bottom side), 21 nets.

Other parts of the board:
AC_IN: Screw_Terminal_01x02; TerminalBlock_MaiXu_MX126-5.0-02P_1x02_P5.00mm
V+: OUT DC 12V; TerminalBlock_MaiXu_MX126-5.0-02P_1x02_P5.00mm
s: LOGO; electric_Shock

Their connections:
/INPUT & RECTIFICATION/AC_IN: AC_IN.1; also elsewhere on the board
/INPUT & RECTIFICATION/AC_OUT: AC_IN.2; also elsewhere on the board
GND: V+.2; also elsewhere on the board
unnamed 17: V+.1; also elsewhere on the board
